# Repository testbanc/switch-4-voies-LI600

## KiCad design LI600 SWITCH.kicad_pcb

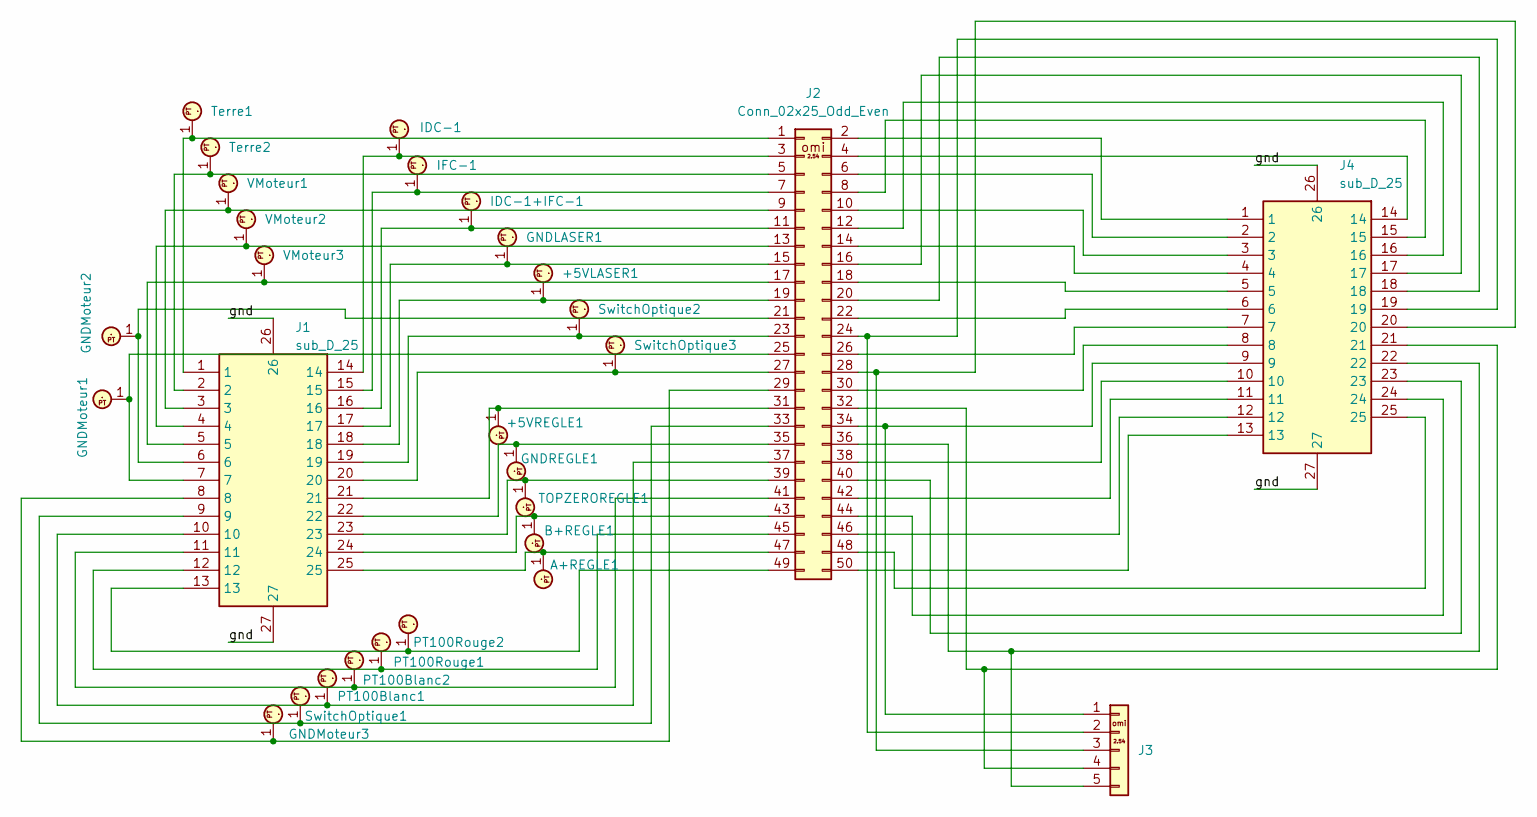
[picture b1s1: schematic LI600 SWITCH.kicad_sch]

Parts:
+5VLASER1, +5VREGLE1: PT_cms_1.0mm; Pt_trad_1.0mm
A+REGLE1: PT_cms_1.0mm; Pt_trad_1.0mm
B+REGLE1: PT_cms_1.0mm; Pt_trad_1.0mm
GNDLASER1: PT_cms_1.0mm; Pt_trad_1.0mm
GNDMoteur1, GNDMoteur2, GNDMoteur3: PT_cms_1.0mm; Pt_trad_1.0mm
GNDREGLE1: PT_cms_1.0mm; Pt_trad_1.0mm
IDC-1, IDC-1+IFC-1: PT_cms_1.0mm; Pt_trad_1.0mm
IFC-1: PT_cms_1.0mm; Pt_trad_1.0mm
J1, J4: sub_D_25; Manufacturer_Part_Number 5443991
J2: Conn_02x25_Odd_Even; PinHeader_2x25_P2.54mm_V_omi
J3: Conn_01x05_P2.54mm_pinheader_vertical; PinHeader_1x05_P2.54mm_V_omi
PT100Blanc1, PT100Blanc2, PT100Rouge1, PT100Rouge2: PT_cms_1.0mm; Pt_trad_1.0mm
SwitchOptique1, SwitchOptique2, SwitchOptique3: PT_cms_1.0mm; Pt_trad_1.0mm
TOPZEROREGLE1: PT_cms_1.0mm; Pt_trad_1.0mm
Terre1: Pt_trad_1.0mm
Terre2: PT_cms_1.0mm; Pt_trad_1.0mm
VMoteur1, VMoteur2, VMoteur3: PT_cms_1.0mm; Pt_trad_1.0mm

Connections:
unnamed: +5VLASER1.1, J1.18, J2.19
unnamed: +5VREGLE1.1, J1.21, J2.31
unnamed: A+REGLE1.1, J1.25, J2.47
unnamed: B+REGLE1.1, J1.24, J2.43
unnamed: GNDLASER1.1, J1.17, J2.15
unnamed: GNDMoteur1.1, J1.7, J2.25
unnamed: GNDMoteur3.1, J1.8, J2.29
unnamed: GNDREGLE1.1, J1.22, J2.35
unnamed: IDC-1+IFC-1.1, J1.16, J2.11
unnamed: IDC-1.1, J1.14, J2.3
unnamed: IFC-1.1, J1.15, J2.7
unnamed: J2.22 (Pin22), J4.6
unnamed: J1.1, J2.1, Terre1.1
unnamed: J2.2, J4.1
unnamed: J2.4, J4.14
unnamed: J1.2, J2.5, Terre2.1
unnamed: J2.6, J4.2
unnamed: J2.8, J4.15
unnamed: J1.3, J2.9, VMoteur1.1
unnamed: J2.10, J4.3
unnamed: J2.12, J4.16
unnamed: J1.4, J2.13, VMoteur2.1
unnamed: J2.14, J4.4
unnamed: J2.16, J4.17
unnamed: J1.5, J2.17, VMoteur3.1
unnamed: J2.18, J4.5
unnamed: J2.20, J4.18
unnamed: J1.19, J2.23, SwitchOptique2.1
unnamed: J2.24, J3.2, J4.19
unnamed: J2.26, J4.7
unnamed: J1.20, J2.27, SwitchOptique3.1
unnamed: J2.28, J3.3, J4.20
unnamed: J2.30, J4.8
unnamed: J2.32, J3.4, J4.21
unnamed: J1.9, J2.33, SwitchOptique1.1
unnamed: J2.34, J3.1, J4.9
unnamed: J2.36, J3.5, J4.22
unnamed: J1.10, J2.37, PT100Blanc1.1
unnamed: J2.38, J4.10
unnamed: J1.23, J2.39, TOPZEROREGLE1.1
unnamed: J2.40, J4.23
unnamed: J1.11, J2.41, PT100Blanc2.1
unnamed: J2.42, J4.11
unnamed: J2.44, J4.24
unnamed: J1.12, J2.45, PT100Rouge1.1
unnamed: J2.46, J4.12
unnamed: J2.48, J4.25
unnamed: J1.13, J2.49, PT100Rouge2.1
unnamed: J2.50, J4.13

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
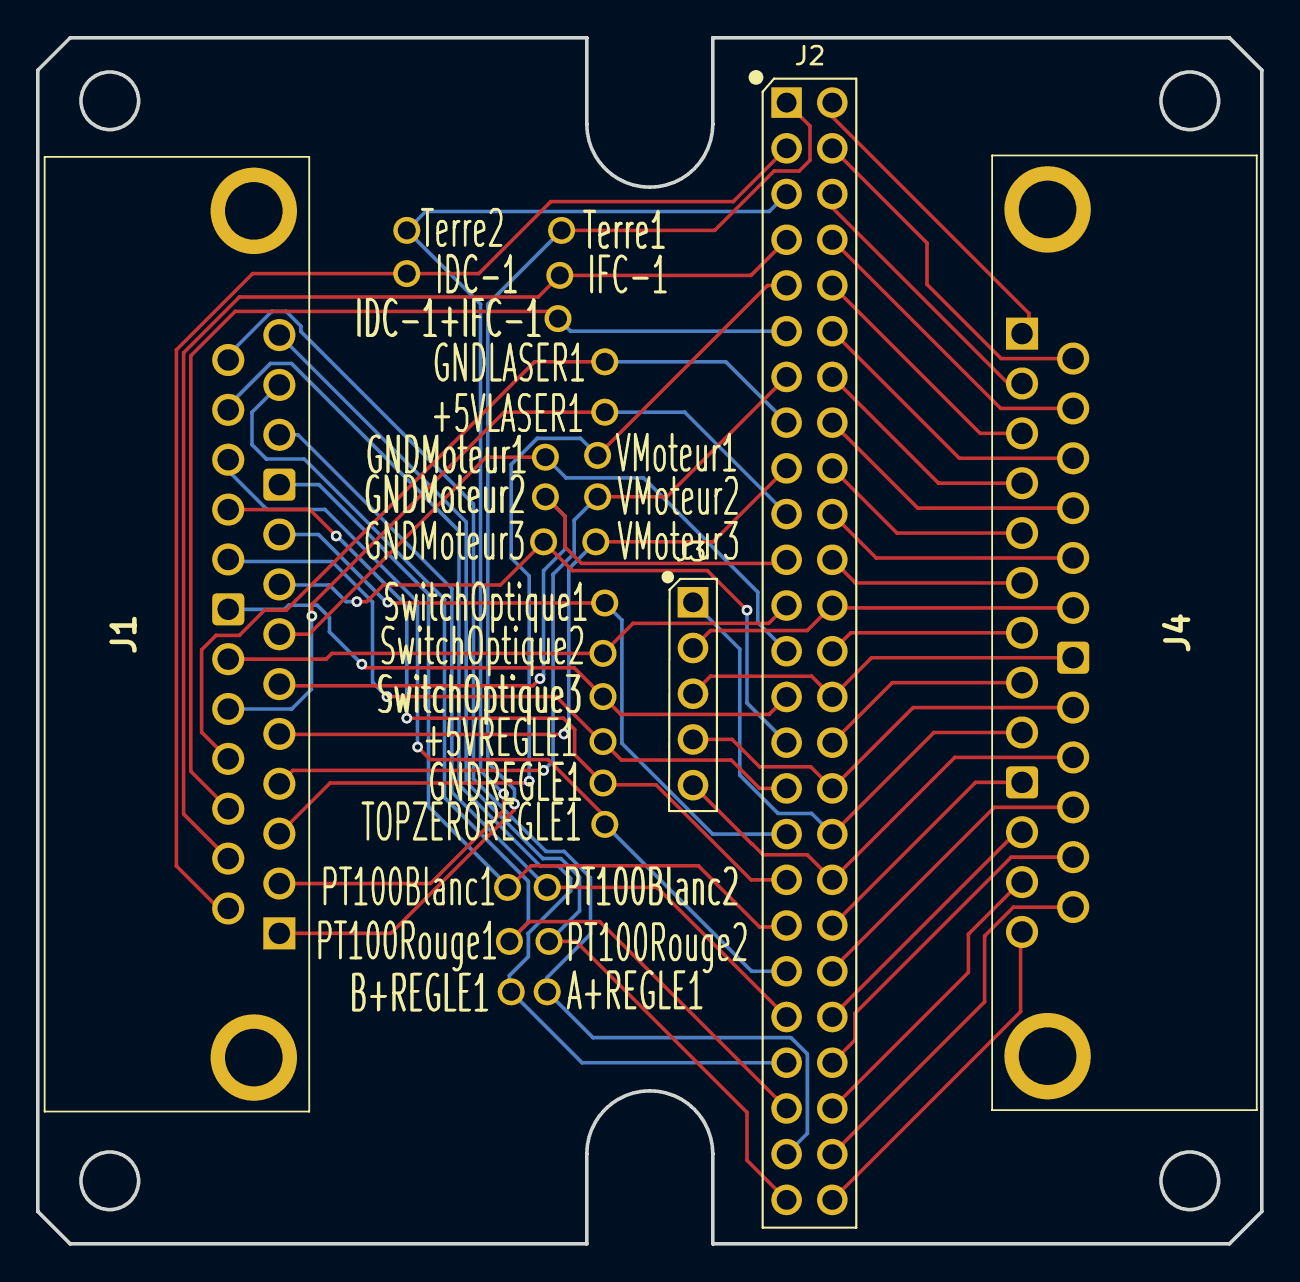
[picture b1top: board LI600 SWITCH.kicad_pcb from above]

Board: 2 copper layers, 68.0 x 67.0 mm, 29 parts (0 on the bottom side), 51 nets.

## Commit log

2024-12-18 version 18/12/2024
2024-12-19 version 19/12/2024
2024-12-19 version finale 19/12/2024
